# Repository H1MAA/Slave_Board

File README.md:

# Slave_Board v2 

#### Removed ULN and Solenoids
#### Removed 12V DC Jack
#### Added IMU MPU6050
#### Improved Routing

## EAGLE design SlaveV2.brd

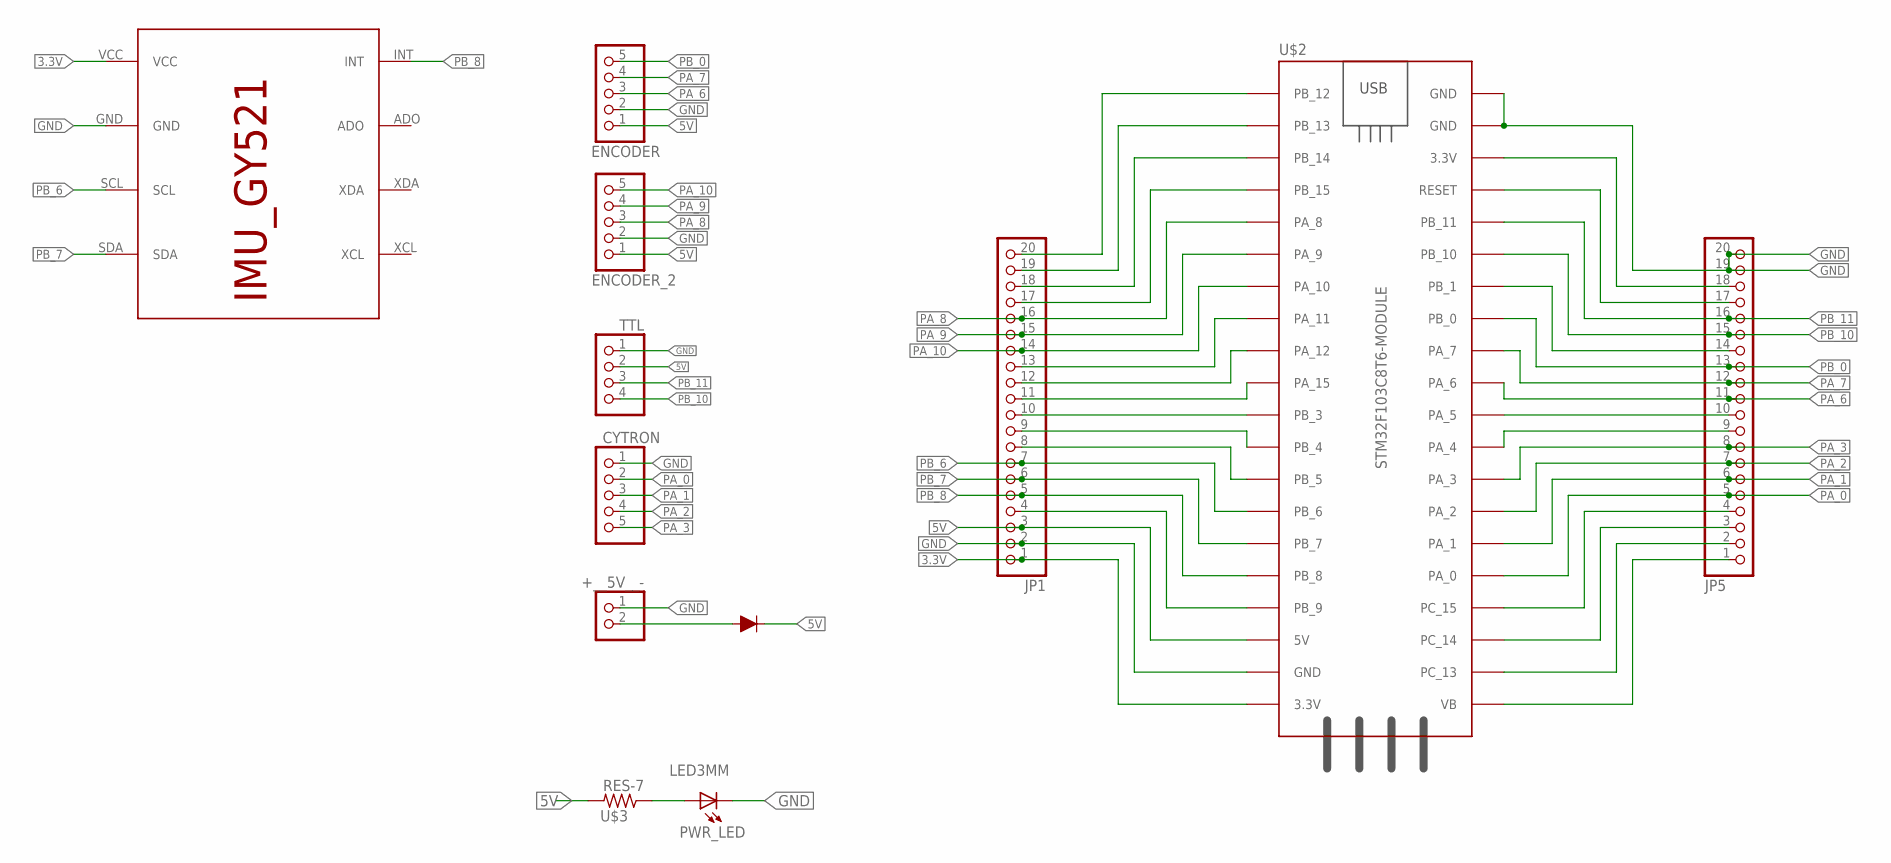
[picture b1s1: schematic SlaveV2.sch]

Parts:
+__5V__-: PINHD-2_DATA; 1X02_DATA
CYTRON: PINHD-5_DATA; 1X05_DATA
D1: 200mA/100V/1V; DIODE-1N4148
ENCODER: PINHD-5_DATA; 1X05_DATA
ENCODER_2: PINHD-5_DATA; 1X05_DATA
IMU: IMU_ROBOCON_GY521; IMU_GY521
JP1, JP5: PINHD-1X20; 1X20
PWR_LED: LED3MM
TTL: PINHD-4_DATA; 1X04_DATA
U$2: STM32F103C8T6-MODULE
U$3: RES-7; 0204/7

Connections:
3.3V: IMU.VCC, JP1.1, U$2.3.3V_1 (3.3V)
3.3V_2: JP5.18, U$2.3.3V_2 (3.3V)
5V: D1.C, ENCODER.1, ENCODER_2.1, JP1.3, TTL.2, U$2.5V, U$3.2
A: PWR_LED.A, U$3.1
GND: +__5V__-.1, CYTRON.1, ENCODER.2, ENCODER_2.2, IMU.GND, JP1.2, JP5.19, JP5.20, PWR_LED.K (C), TTL.1, U$2.GND_1 (GND), U$2.GND_2 (GND), U$2.GND_3 (GND)
unnamed: JP1.10, U$2.PB_3
unnamed: JP1.11, U$2.PA_15
unnamed: JP1.12, U$2.PA_12
unnamed: JP1.13, U$2.PA_11
unnamed: JP1.17, U$2.PB_15
unnamed: JP1.18, U$2.PB_14
unnamed: JP1.19, U$2.PB_13
unnamed: JP1.20, U$2.PB_12
unnamed: JP1.9, U$2.PB_4
unnamed: JP1.8, U$2.PB_5
unnamed: JP1.4, U$2.PB_9
unnamed: JP5.10, U$2.PA_5
unnamed: JP5.14, U$2.PB_1
unnamed: JP5.17, U$2.RESET
unnamed: +__5V__-.2, D1.A
unnamed: JP5.9, U$2.PA_4
unnamed: JP5.4, U$2.PC_15
unnamed: JP5.3, U$2.PC_14
unnamed: JP5.2, U$2.PC_13
unnamed: JP5.1, U$2.VB
PA_0: CYTRON.2, JP5.5, U$2.PA_0
PA_1: CYTRON.3, JP5.6, U$2.PA_1
PA_2: CYTRON.4, JP5.7, U$2.PA_2
PA_3: CYTRON.5, JP5.8, U$2.PA_3
PA_6: ENCODER.3, JP5.11, U$2.PA_6
PA_7: ENCODER.4, JP5.12, U$2.PA_7
PA_8: ENCODER_2.3, JP1.16, U$2.PA_8
PA_9: ENCODER_2.4, JP1.15, U$2.PA_9
PA_10: ENCODER_2.5, JP1.14, U$2.PA_10
PB_0: ENCODER.5, JP5.13, U$2.PB_0
PB_6: IMU.SCL, JP1.7, U$2.PB_6
PB_7: IMU.SDA, JP1.6, U$2.PB_7
PB_8: IMU.INT, JP1.5, U$2.PB_8
PB_10: JP5.15, TTL.4, U$2.PB_10
PB_11: JP5.16, TTL.3, U$2.PB_11

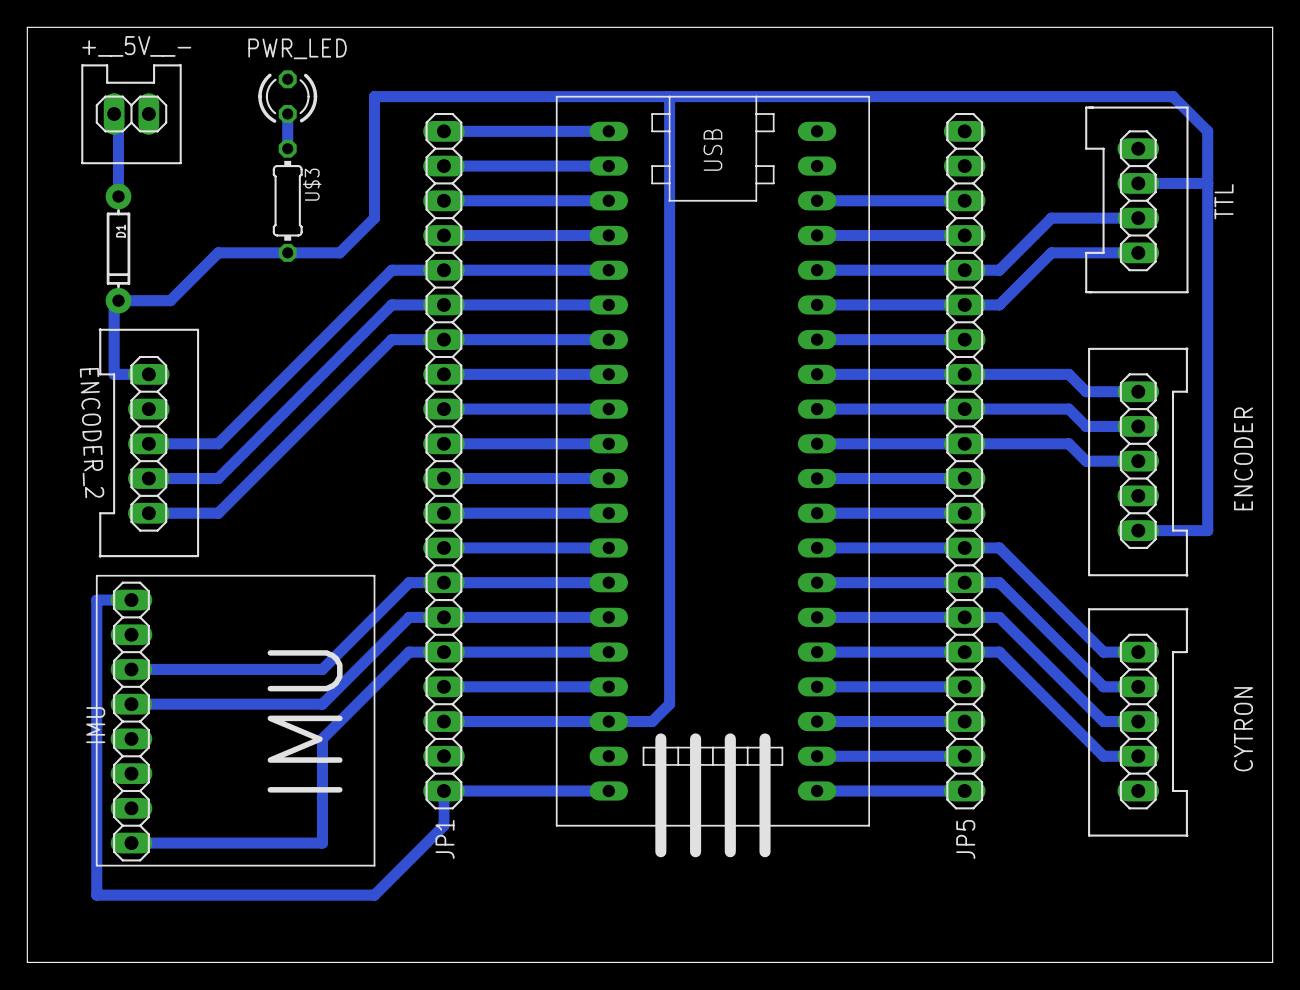
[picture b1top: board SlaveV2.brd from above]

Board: 2 copper layers, 91.1 x 68.4 mm, 12 parts (0 on the bottom side), 40 nets.

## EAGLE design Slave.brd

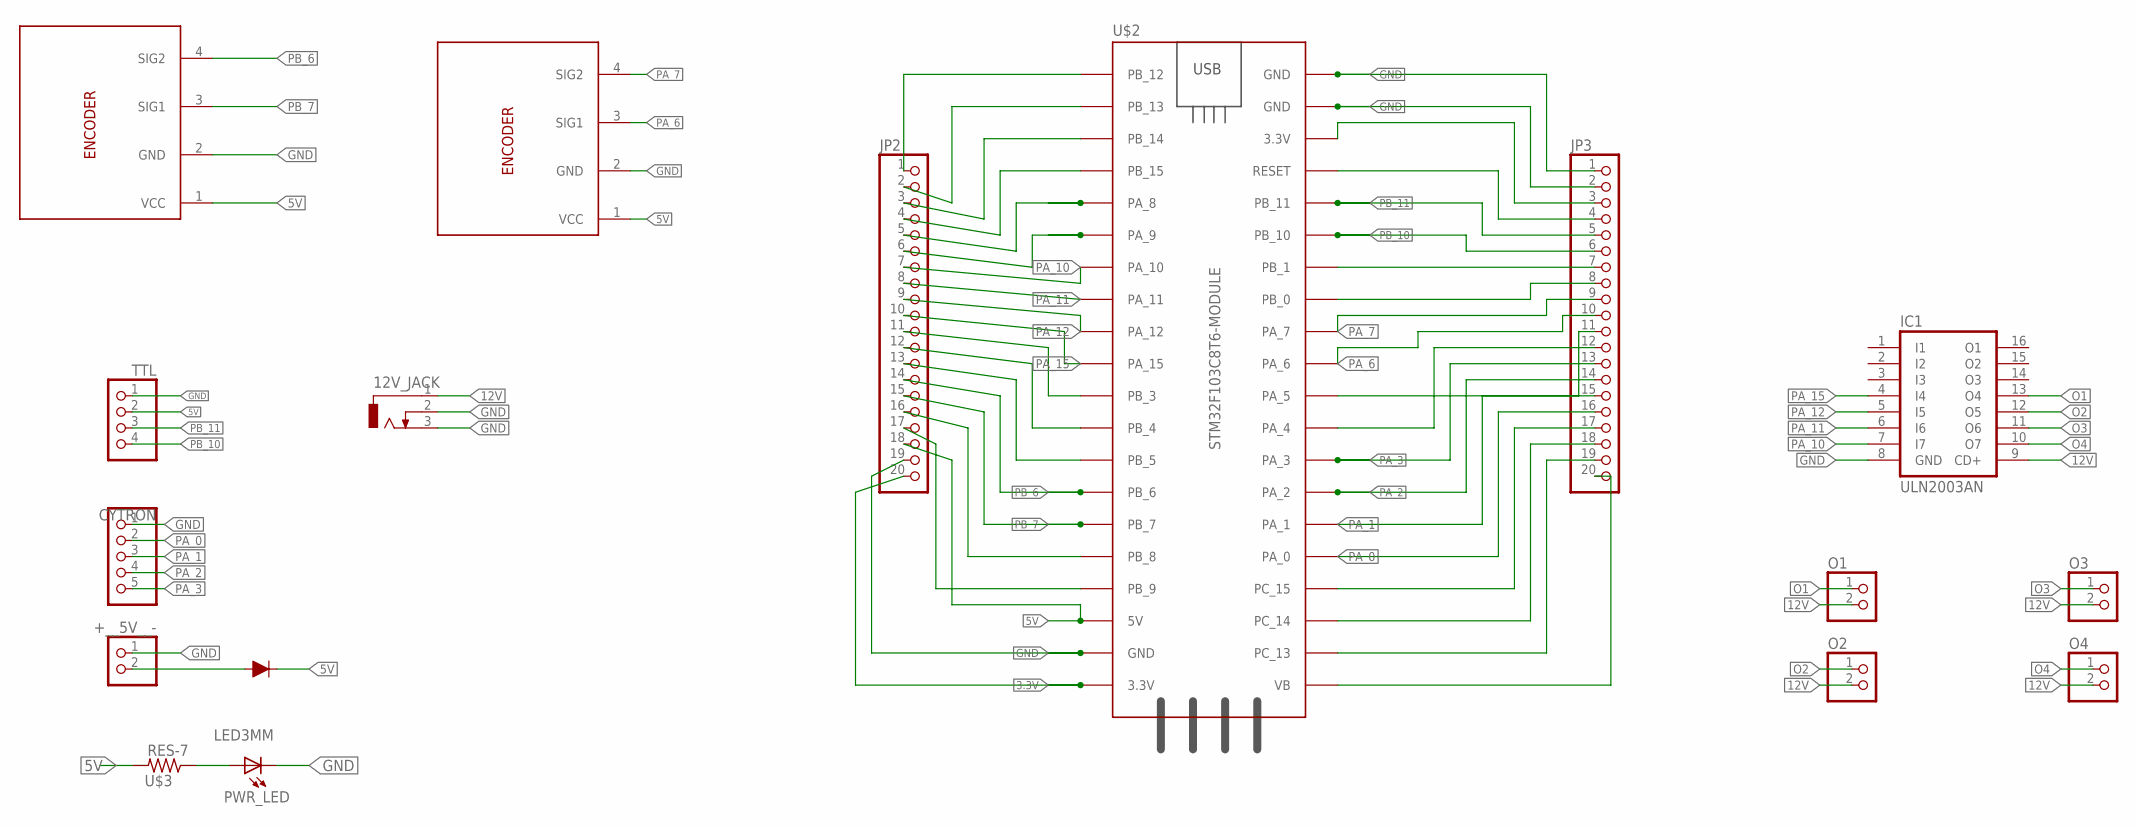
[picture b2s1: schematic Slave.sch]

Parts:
12V_JACK: CON_JACK; DCJ0303
+__5V__-: PINHD-2_DATA; 1X02_DATA
CYTRON: PINHD-5_DATA; 1X05_DATA
D1: 200mA/100V/1V; DIODE-1N4148
IC1: ULN2003AN; DIL16
JP2, JP3: PINHD-1X20; 1X20
O1, O2, O3, O4: PINHD-2_DATA; 1X02_DATA
PWR_LED: LED3MM
TTL: PINHD-4_DATA; 1X04_DATA
U$1, U$5: ENCODER; 1X04_DATA
U$2: STM32F103C8T6-MODULE
U$3: RES-7; 0204/7

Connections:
3.3V: JP2.20, U$2.3.3V_1 (3.3V)
5V: D1.C, JP2.18, TTL.2, U$1.1 (VCC), U$2.5V, U$3.2, U$5.1 (VCC)
12V: 12V_JACK.1, IC1.9 (CD+), O1.2, O2.2, O3.2, O4.2
A: PWR_LED.A, U$3.1
GND: 12V_JACK.2, 12V_JACK.3, +__5V__-.1, CYTRON.1, IC1.8 (GND), JP2.19, JP3.1, JP3.2, PWR_LED.K (C), TTL.1, U$1.2 (GND), U$2.GND_1 (GND), U$2.GND_2 (GND), U$2.GND_3 (GND), U$5.2 (GND)
unnamed: JP3.20, U$2.VB
unnamed: JP3.19, U$2.PC_13
unnamed: JP3.18, U$2.PC_14
unnamed: JP3.17, U$2.PC_15
unnamed: JP3.12, U$2.PA_4
unnamed: JP3.3, U$2.3.3V_2 (3.3V)
unnamed: JP3.4, U$2.RESET
unnamed: JP3.7, U$2.PB_1
unnamed: JP3.8, U$2.PB_0
unnamed: JP3.11, U$2.PA_5
unnamed: JP2.1, U$2.PB_12
unnamed: JP2.2, U$2.PB_13
unnamed: JP2.3, U$2.PB_14
unnamed: JP2.4, U$2.PB_15
unnamed: JP2.11, U$2.PB_3
unnamed: JP2.12, U$2.PB_4
unnamed: JP2.13, U$2.PB_5
unnamed: JP2.16, U$2.PB_8
unnamed: JP2.17, U$2.PB_9
unnamed: +__5V__-.2, D1.A
O1: IC1.13 (O4), O1.1
O2: IC1.12 (O5), O2.1
O3: IC1.11 (O6), O3.1
O4: IC1.10 (O7), O4.1
PA_0: CYTRON.2, JP3.16, U$2.PA_0
PA_1: CYTRON.3, JP3.15, U$2.PA_1
PA_2: CYTRON.4, JP3.14, U$2.PA_2
PA_3: CYTRON.5, JP3.13, U$2.PA_3
PA_6: JP3.10, U$1.3 (SIG1), U$2.PA_6
PA_7: JP3.9, U$1.4 (SIG2), U$2.PA_7
PA_8: JP2.5, U$2.PA_8
PA_9: JP2.6, U$2.PA_9
PA_10: IC1.7 (I7), JP2.7, U$2.PA_10
PA_11: IC1.6 (I6), JP2.8, U$2.PA_11
PA_12: IC1.5 (I5), JP2.9, U$2.PA_12
PA_15: IC1.4 (I4), JP2.10, U$2.PA_15
PB_6: JP2.14, U$2.PB_6, U$5.4 (SIG2)
PB_7: JP2.15, U$2.PB_7, U$5.3 (SIG1)
PB_10: JP3.6, TTL.4, U$2.PB_10
PB_11: JP3.5, TTL.3, U$2.PB_11

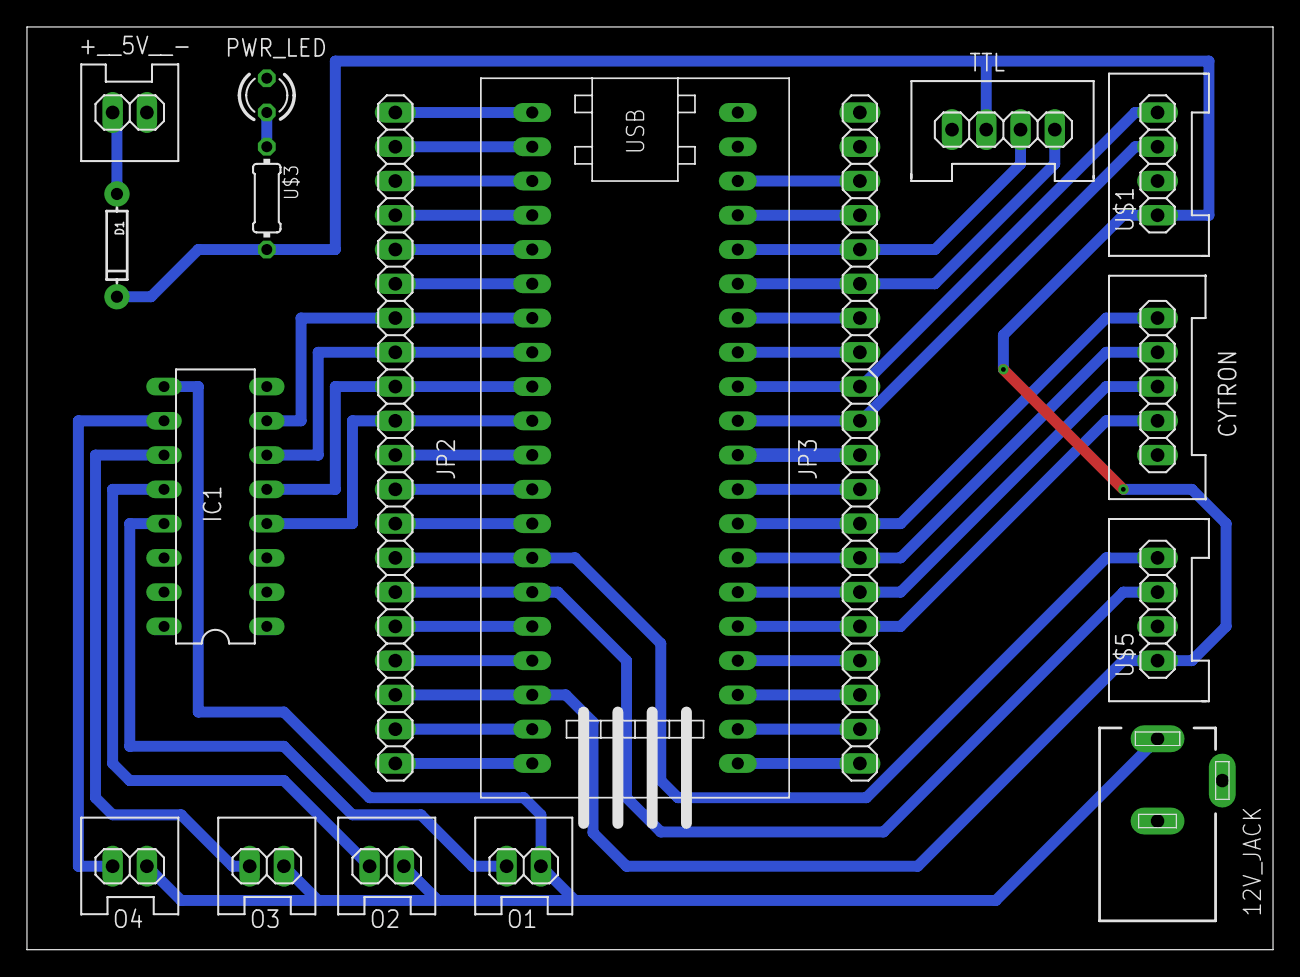
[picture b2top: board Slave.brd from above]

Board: 2 copper layers, 92.4 x 68.4 mm, 17 parts (0 on the bottom side), 45 nets.
